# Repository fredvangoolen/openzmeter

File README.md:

Description
===============

openzmeter (oZm) is an Open Source system designed for power quality analysis and smart energy metering in power networks.
It has been designed to comply with international standards IEC 61000-4-30 and EN 50160. It is able to measure RMS voltages with an accuracy up to 0.1%, frequency up to 10 mHz (between 42.5 and 57.5 Hz) and RMS currents according to different sensor probes (the basic version can handle up to 400 V and 50 A RMS using an onboard Hall effect sensor with a precision of 1%).

See http://www.openzmeter.com

Fluvius digital meter (S1 port) support
===============

This fork adds support for the **S1 port** of the digital electricity meters installed by Fluvius in Flanders
(Belgium). Instead of openZmeter's own capture hardware, the meter itself provides the measurements: it continuously
streams instantaneous voltage and current samples of all phases (and the neutral, if the meter provides it), at
2 to 4 kHz. openZmeter analyzes these samples like those from its own hardware, giving RMS values, active/reactive
power and energy, frequency, harmonics, events, alarms, cyclic histograms, MQTT and tariffs.

* **Specification**: e-MUCS H ed. 1.3, section 4, published by
  [Fluvius](https://www.fluvius.be/sites/fluvius/files/2019-12/e-mucs_h_ed_1_3.pdf).
* **Activation**: the S1 port is off by default. Ask Fluvius to activate it for your meter.
* **Hardware**: a USB to RS-422 adapter that can receive at exactly 2 Mbaud (e.g. FTDI FT232R/FT232H based) connected
  to the RJ12 S1 socket of the meter: pin 3 = GND, pin 4 = BUS- and pin 5 = BUS+. The line needs one 120 Ω termination
  on the adapter side (built into the FTDI USB-RS422-WE cable). Check the pin numbering first: on the Sagemcom meter
  tested here, pin 1 is the **rightmost** contact when facing the socket. Wire colours for the FTDI USB-RS422-WE cable
  are in the [S1 driver README](Service/Source/Devices/S1/README.md#wiring-an-ftdi-usb-rs422-we-cable).
* **Check the connection first**: [`Service/Utils/S1Monitor`](Service/Utils/S1Monitor) is a small standalone tool
  (only needs `g++`). It shows frame rate, errors, meter info, frequency, RMS values and power every second, and
  explains what is wrong when nothing valid arrives. Build it with `make` and run `./s1monitor /dev/ttyUSB0`.
* **Check the results**: [`Service/Utils/P1Monitor`](Service/Utils/P1Monitor) reads the P1 port of the same meter and
  compares its voltage, current, power and energy registers with what openZmeter measured on S1.
* **Tests without a meter**: [`Service/Utils/S1Test`](Service/Utils/S1Test) has unit tests and a simulated meter.
* **Single board computer**: a Raspberry Pi 4 (2 GB is enough) works well. Run
  `sudo Service/Packaging/raspberrypi/install.sh` to build and install openZmeter with a local PostgreSQL database,
  a systemd service and a watchdog that restarts openZmeter when its web interface stops answering. Then enable the
  device under *Settings » Devices » S1*. If port 80 is already taken (for example by Pi-hole), add `--http-port 8080`.
* **Analyzer**: created when the first valid frame arrives, as "Fluvius S1 meter" with time zone Europe/Brussels. Both
  can be changed in its settings.
* **Clock**: the meter announces its sample rate only roughly, so the driver measures it against the system clock. Keep
  the clock synchronized (NTP, the default on Raspberry Pi OS).
* **Limitations**: because of the lower sample rate, harmonics above roughly the 25th to 40th order (depending on the
  meter) are reported as 0.

Details are in the [S1 driver README](Service/Source/Devices/S1/README.md). Architecture, data flow and storage
notes are in [`Docs/NOTES.md`](Docs/NOTES.md).

License and changes
===============

This is a **modified version of openZmeter**. The original is [eauel/openzmeter](https://github.com/eauel/openzmeter)
([openzmeter.com](https://openzmeter.com)). Modified by [fredvangoolen](https://github.com/fredvangoolen) since
19 November 2026: support for the S1 port of Fluvius digital meters, an installer for the Raspberry Pi, test tools, and
corrections to existing calculations (listed in [`Docs/NOTES.md`](Docs/NOTES.md)). The commit history has all changes
with their dates.

Like the original, it is licensed under the GNU General Public License, version 3 or (as stated in the source files) any
later version: see [`LICENSE`](LICENSE). It comes without any warranty. Libraries in `Service/Libs` have their own licenses, included there.

This project is not affiliated with or endorsed by Fluvius, FTDI or the makers of openZmeter. Product names are only used
to describe what it works with.

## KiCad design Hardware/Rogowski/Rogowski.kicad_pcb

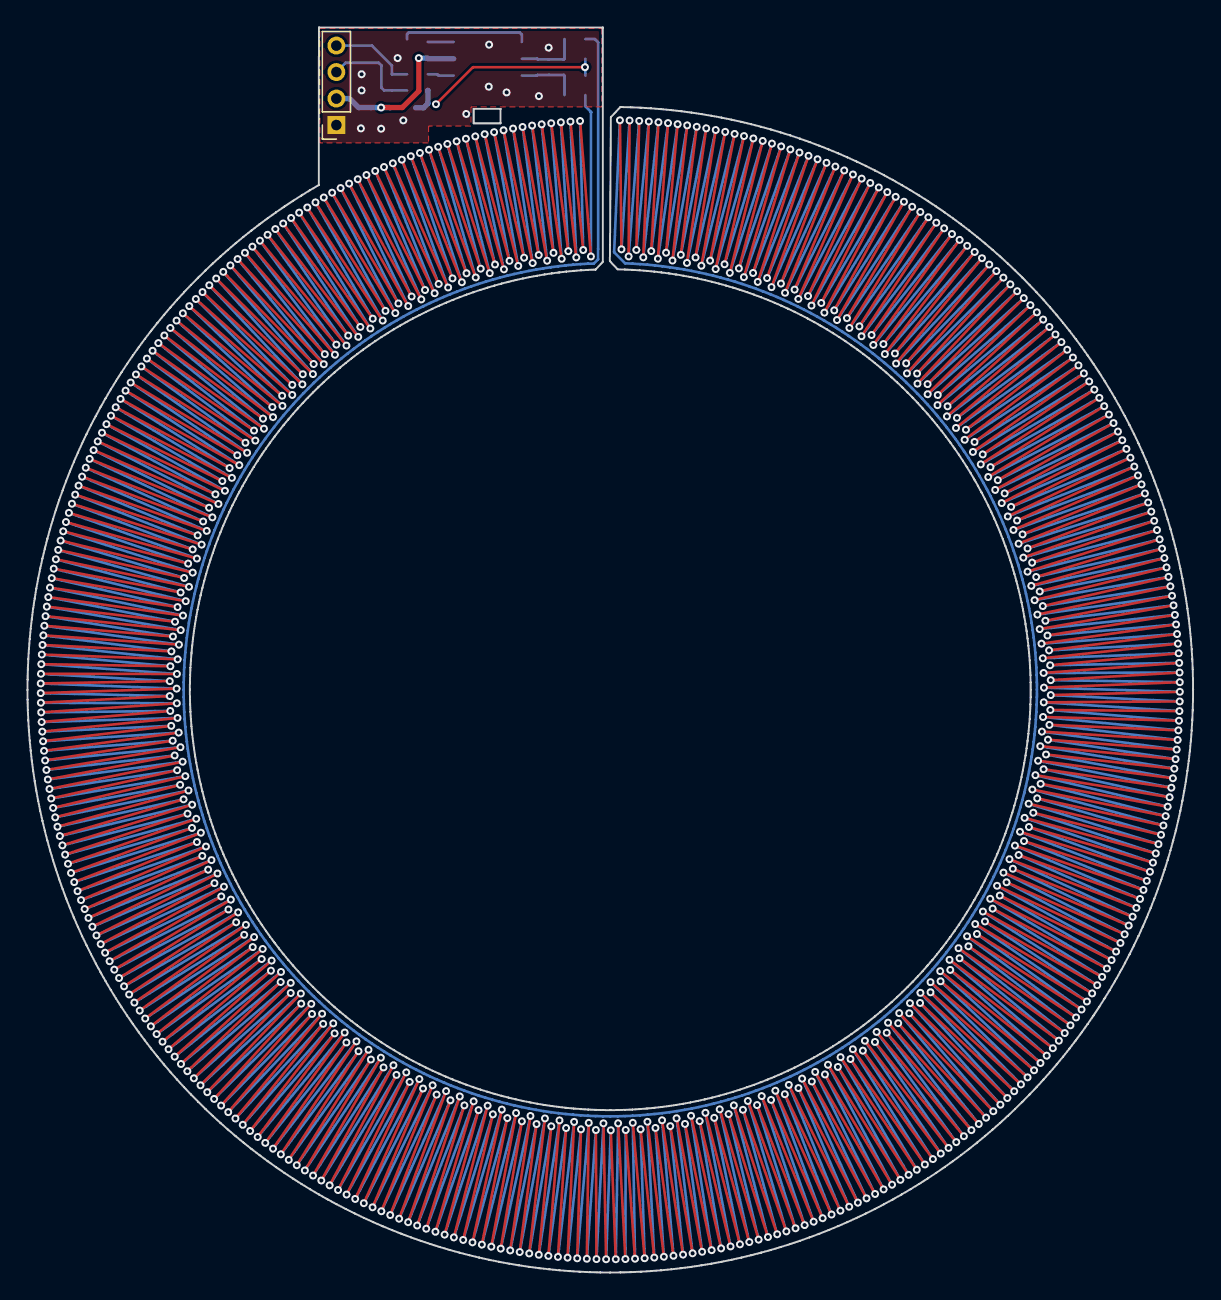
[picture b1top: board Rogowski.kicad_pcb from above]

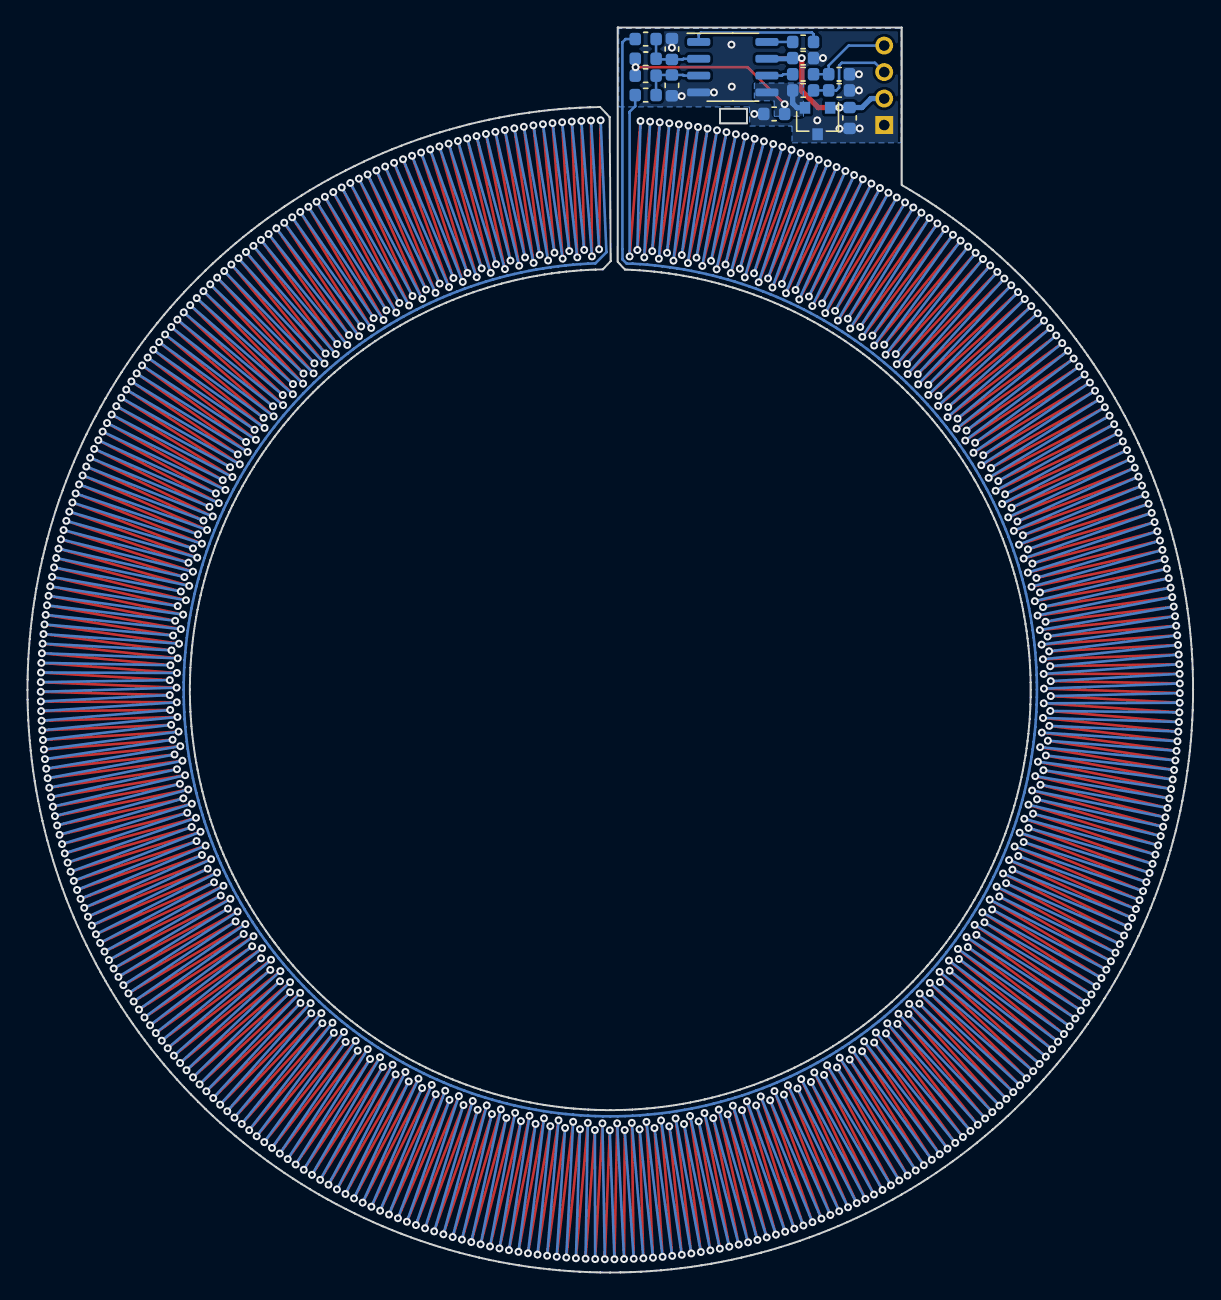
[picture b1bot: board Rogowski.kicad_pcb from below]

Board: 2 copper layers, 88.0 x 94.0 mm, 17 parts (16 on the bottom side), 11 nets.

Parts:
C1, C2, C3, C4, C5, C6, C7: C_Small; C_0603_1608Metric
J1: Conn_01x04_Female; PinSocket_1x04_P2.00mm_Vertical
R1, R2, R3, R4, R5, R6, R7: R_Small; R_0603_1608Metric
U1: INA128; SO-8_3.9x4.9mm_P1.27mm
U2: MCP1525-TT; SOT-23

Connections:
2.5V: C7.2, R3.1, R4.2, R7.2, U1.5, U2.2
5V: C3.2, C4.2, J1.2, U1.7, U2.1
GND: C1.2, C2.1, C3.1, C4.1, C5.2, C6.1, C7.1, J1.1, U1.4, U2.3
unnamed: C1.1, R1.1, R3.2, U1.3
unnamed: C2.2, R2.1, R4.1, U1.2
unnamed: C5.1, J1.4, R6.1
unnamed: C6.2, J1.3, R7.1
unnamed: R1.2, R2.2
unnamed: R5.1, U1.8
unnamed: R5.2, U1.1
unnamed: R6.2, U1.6

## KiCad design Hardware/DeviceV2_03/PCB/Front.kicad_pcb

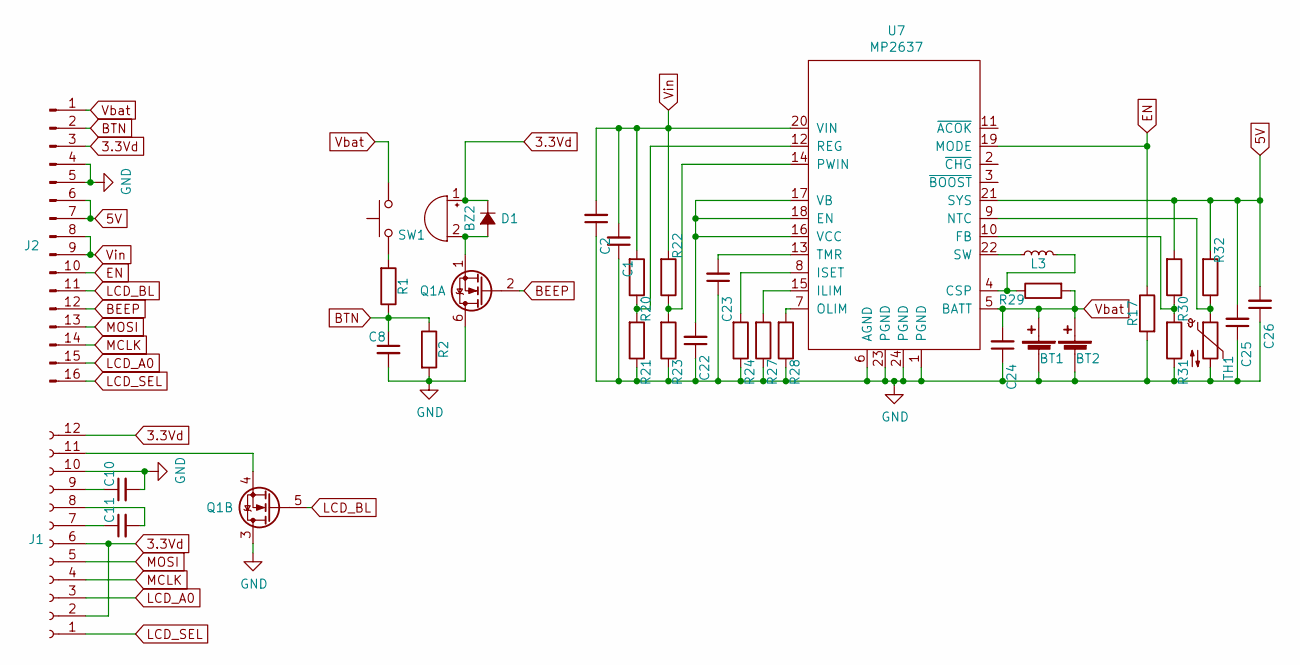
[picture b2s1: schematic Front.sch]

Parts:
BT1, BT2: Battery clips; 18500_Clips
BZ2: QMB-09B-05; MLT-5030
C1, C2, C25, C26: 100nF 25v; C_0805_2012Metric
C8, C10, C11, C22, C23, C24: 100nF 25v; C_0603_1608Metric
D1: D_Small_ALT-3Phase-rescue; D_SOD-323
J1: Conn_01x12_Female; LCD_52.3x40.2
J2: Conn_01x06_Male; PinHeader_1x16_P2.54mm_Vertical
L3: L_Small; MWSA0503S
Q1: SSM6N7002KFU; SOT-363_SC-70-6
R1, R2, R17, R20, R21, R22, R23, R24, R27, R28, R30, R31, R32: 100k; R_0603_1608Metric
R29: 100k; R_1206_3216Metric
SW1: SW_Push-3Phase-rescue; SW_Push_4.5x4.5mm_H8mm
TH1: Thermistor_NTC-3Phase-rescue; R_0603_1608Metric
U7: MP2637; QFN-24_4x4mm_P0.5mm

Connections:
3.3Vd: BZ2.1 (-), D1.1 (K), J1.2, J1.6, J1.12, J2.3
5V: C25.2, C26.2, J2.6, J2.7, R30.2, R32.2, U7.21 (SYS)
BEEP: J2.12, Q1.2 (G)
BTN: C8.1, J2.2, R1.1, R2.1
EN: J2.10, R17.1, U7.19 (MODE)
GND: BT1.2 (-), BT2.2 (-), C1.1, C2.1, C8.2, C10.2, C22.1, C23.1, C24.1, C25.1, C26.1, J1.10, J2.4, J2.5, Q1.3 (D), Q1.6 (D), R2.2, R17.2, R21.1, R23.1, R24.1, R27.1, R28.1, R31.1, TH1.2, U7.1 (PGND), U7.6 (AGND), U7.23 (PGND), U7.24 (PGND)
LCD_A0: J1.3, J2.15
LCD_BL: J2.11, Q1.5 (G)
LCD_SEL: J1.1, J2.16
MCLK: J1.4, J2.14
MOSI: J1.5, J2.13
unnamed: BZ2.2 (+), D1.2 (A), Q1.1 (S)
unnamed: C10.1, J1.9
unnamed: C11.1, J1.7
unnamed: C11.2, J1.8
unnamed: C22.2, U7.16 (VCC), U7.17 (VB), U7.18 (EN)
unnamed: C23.2, U7.13 (TMR)
unnamed: J1.11, Q1.4 (S)
unnamed: L3.1, R29.1, U7.4 (CSP)
unnamed: L3.2, U7.22 (SW)
unnamed: R1.2, SW1.2
unnamed: R20.1, R21.2, U7.12 (REG)
unnamed: R22.1, R23.2, U7.14 (PWIN)
unnamed: R24.2, U7.8 (ISET)
unnamed: R27.2, U7.15 (ILIM)
unnamed: R28.2, U7.7 (OLIM)
unnamed: R30.1, R31.2, U7.10 (FB)
unnamed: R32.1, TH1.1, U7.9 (NTC)
Vbat: BT1.1 (+), BT2.1 (+), C24.2, J2.1, R29.2, SW1.1, U7.5 (BATT)
Vin: C1.2, C2.2, J2.8, J2.9, R20.2, R22.2, U7.20 (VIN)

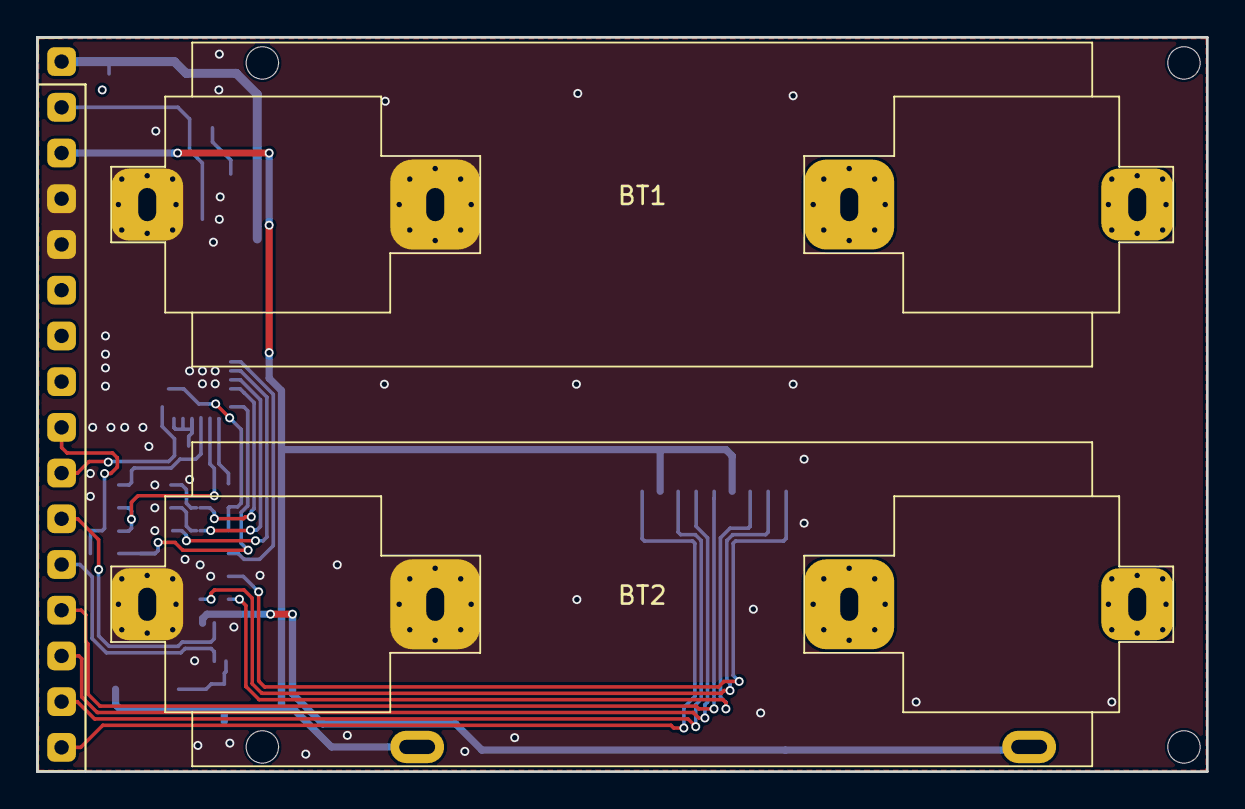
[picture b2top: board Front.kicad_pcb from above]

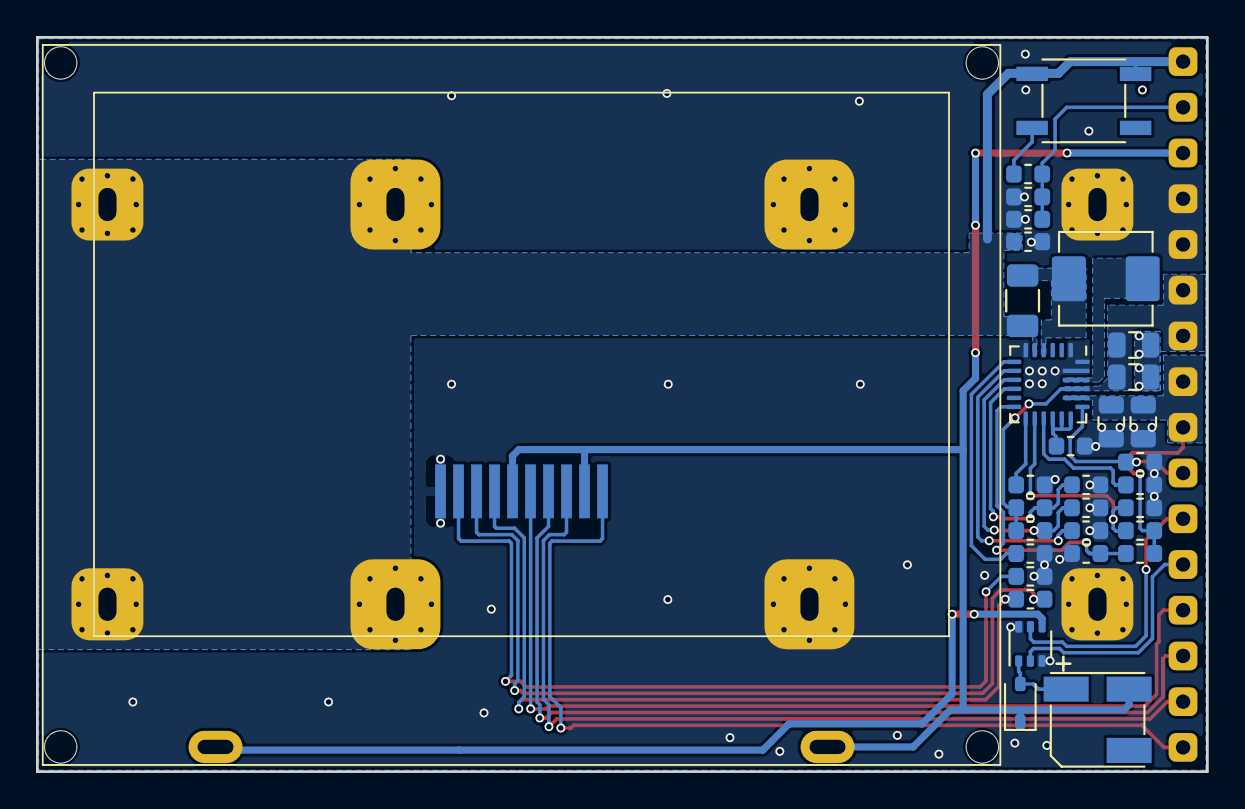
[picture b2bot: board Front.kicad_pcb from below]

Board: 2 copper layers, 65.0 x 40.8 mm, 35 parts (32 on the bottom side), 30 nets.

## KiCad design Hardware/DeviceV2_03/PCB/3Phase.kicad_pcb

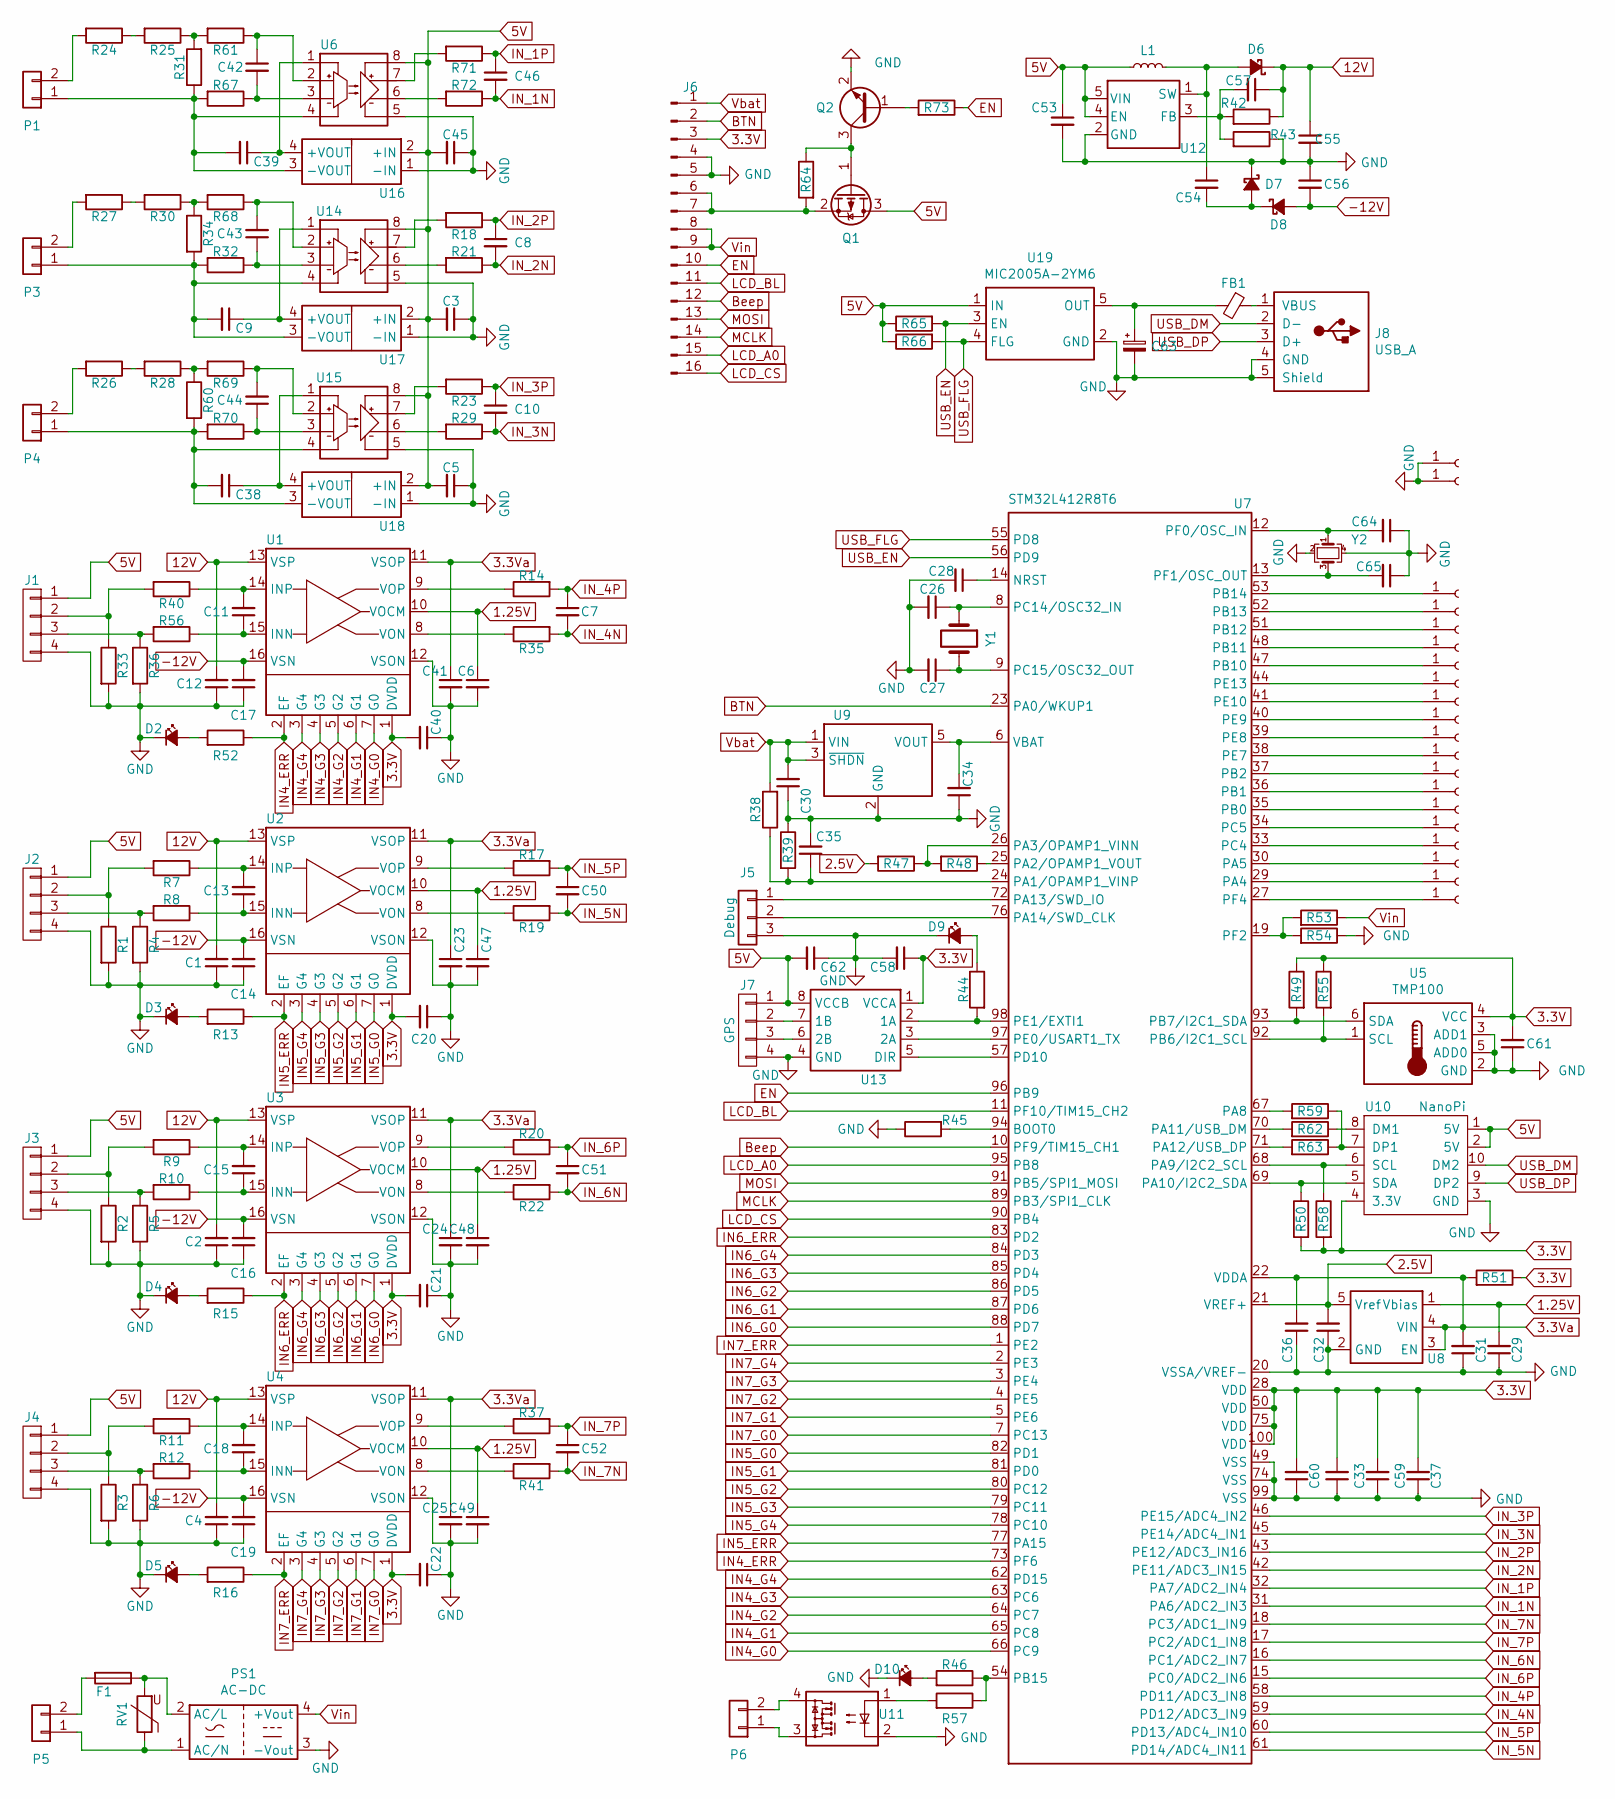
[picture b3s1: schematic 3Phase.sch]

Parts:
C1, C2, C3, C4, C5, C6, C7, C9, C11, C12, C13, C14, C15, C16, C17, C18, C19, C20, C21, C22, C23, C24, C25, C28, C29, C30, C31, C32, C33, C34, C35, C36, C37, C38, C40, C41, C43, C44, C45, C47, C48, C49, C50, C51, C52, C53, C54, C55, C56, C57, C59, C60, C61: 100nF 25v; C_0603_1608Metric
C8, C10, C42, C46: 330pF NP0; C_0603_1608Metric
C26, C27: 6pF; C_0603_1608Metric; LCSC C130125
C39: 100nF 10v; C_0603_1608Metric
C58, C62: 100nF; C_0603_1608Metric; LCSC C14663
C63: CP_Small; CP_EIA-3528-21_Kemet-B
C64, C65: 20pF; C_0603_1608Metric; LCSC C105621
D2, D10: LED_Small_ALT; LED_0603_1608Metric
D3, D4, D5, D9: LED; LED_0603_1608Metric; LCSC C1322294
D6, D7, D8: D_Schottky_Small_ALT; D_SOD-323
F1: Fuse; Fuse_Littelfuse_395Series
FB1: BLM18KG601SZ1D; L_0603_1608Metric
J1, J2, J3, J4, J7: 95001-6P6C; KF2EDGR_2.54x4
J5: 95001-6P6C; PinHeader_1x03_P2.54mm_Vertical
J6: Conn_01x16_Male; PinHeader_1x16_P2.54mm_Vertical
J8: USB_A; USB_A_Molex_67643_Horizontal
J9, J10, J11, J12, J13, J14, J15, J16, J17, J20, J22, J23, J25, J26, J27, J28, J29, J30, J31, J32: Conn_01x01_Female; TestPoint_1.8mm
L1: L_Small; L_1210_3225Metric
P1, P3, P4, P5, P6: 3.81x4 terminal block; PhoenixContact_MC_1,5_2-G-3.81_1x02_P3.81mm_Horizontal
PS1: AC-DC; AC-DC_Aliexpress
Q1: Si2319CDS; SOT-23
Q2: MMBT3904; SOT-23
R1, R2, R3, R4, R5, R6, R7, R8, R9, R10, R11, R12, R32, R33, R34, R36, R38, R39, R40, R42, R43, R45, R46, R47, R48, R49, R51, R53, R54, R55, R56, R57, R59, R60, R62, R63, R64, R65, R66, R68, R69, R70, R73: 2.2k; R_0603_1608Metric
R13, R15, R16, R44, R52: 470; R_0603_1608Metric; LCSC C114669
R14, R17, R19, R20, R22, R35, R37, R41: 100h; R_0603_1608Metric
R18, R21, R23, R29, R61, R67, R71, R72: 12; R_0603_1608Metric
R24, R25: 499k; R_1206_3216Metric; LCSC C517514
R26, R27, R28, R30: 200k; R_1206_3216Metric
R31: 1k02; R_0603_1608Metric; LCSC C705734
R50, R58: 4k7; R_0603_1608Metric; LCSC C99782
RV1: 05D391K; RV_Disc_D7mm_W3.4mm_P5mm
U1, U2, U3, U4: PGA281; TSSOP-16_4.4x5mm_P0.65mm; LCSC C69359
U5: TMP100; SOT-23-6
U6, U14, U15: SI8921BB; SOIC-8_3.9x4.9mm_P1.27mm
U7: STM32L412R8T6; LQFP-100_14x14mm_P0.5mm
U8: REF2025; SOT-23-5
U9: MCP1811; SOT-23-5
U10: NanoPi; NanoPI_Air
U11: SSR_MOSFET_DIP4; DIP-4_W7.62mm
U12: LM27313XMF; SOT-23-5
U13: SN74LVC2T45DCUTG4; VSSOP-8_2.3x2mm_P0.5mm; LCSC C2677407
U16, U17, U18: B0505D-1W; Converter_DCDC_muRata_CRE1xxxxxx3C_THT
U19: MIC2005A-2YM6; SOT-23-5
Y1: 32.768kHz; Crystal_SMD_3215-2Pin_3.2x1.5mm; LCSC C94673
Y2: 8MHz; Crystal_SMD_3225-4Pin_3.2x2.5mm; LCSC C389817

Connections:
1.25V: C6.1, C29.2, C47.1, C48.1, C49.1, U1.10 (VOCM), U2.10 (VOCM), U3.10 (VOCM), U4.10 (VOCM), U8.1 (Vbias)
2.5V: C32.2, R47.2, U7.21 (VREF+), U8.5 (Vref)
3.3V: C20.2, C21.2, C22.2, C33.2, C37.2, C40.2, C58.1, C59.2, C60.2, C61.2, J6.3, R49.1, R50.2, R51.1, R55.1, R58.2, U1.1 (DVDD), U2.1 (DVDD), U3.1 (DVDD), U4.1 (DVDD), U5.4 (VCC), U7.28 (VDD), U7.50 (VDD), U7.75 (VDD), U7.100 (VDD), U10.4 (3.3V), U13.1 (VCCA)
3.3Va: C23.1, C24.1, C25.1, C31.2, C36.2, C41.1, R51.2, U1.11 (VSOP), U2.11 (VSOP), U3.11 (VSOP), U4.11 (VSOP), U7.22 (VDDA), U8.3 (EN), U8.4 (VIN)
5V: C3.2, C5.2, C45.2, C53.1, C62.2, J1.1, J2.1, J3.1, J4.1, J7.1, L1.1, Q1.3 (D), R65.1, R66.1, U6.8 (VDD2), U10.1 (5V), U10.2 (5V), U12.4 (EN), U12.5 (VIN), U13.8 (VCCB), U14.8 (VDD2), U15.8 (VDD2), U16.2 (+IN), U17.2 (+IN), U18.2 (+IN), U19.1 (IN)
12V: C1.2, C2.2, C4.2, C12.2, C55.1, C57.1, D6.1 (K), R42.1, U1.13 (VSP), U2.13 (VSP), U3.13 (VSP), U4.13 (VSP)
-12V: C14.2, C16.2, C17.2, C19.2, C56.2, D8.2 (A), U1.16 (VSN), U2.16 (VSN), U3.16 (VSN), U4.16 (VSN)
BTN: J6.2, U7.23 (PA0/WKUP1)
Beep: J6.12, U7.10 (PF9/TIM15_CH1)
EN: J6.10, R73.1, U7.96 (PB9)
GND: C1.1, C2.1, C3.1, C4.1, C5.1, C6.2, C12.1, C14.1, C16.1, C17.1, C19.1, C20.1, C21.1, C22.1, C23.2, C24.2, C25.2, C26.2, C27.2, C28.2, C29.1, C30.1, C31.1, C32.1, C33.1, C34.1, C35.2, C36.1, C37.1, C40.1, C41.2, C45.1, C47.2, C48.2, C49.2, C53.2, C55.2, C56.1, C58.2, C59.1, C60.1, C61.1, C62.1, C63.2, C64.1, C65.1, D2.1 (K), D3.1 (K), D4.1 (K), D5.1 (K), D7.1 (K), D9.1 (K), D10.1 (K), J1.4, J2.4, J3.4, J4.4, J5.3, J6.4, J6.5, J7.4, J8.4 (GND), J8.5 (Shield), J17.1, J32.1, PS1.3 (-Vout), Q2.2 (E), R1.2, R2.2, R3.2, R4.2, R5.2, R6.2, R33.2, R36.2, R39.1, R43.1, R45.1, R54.1, U1.12 (VSON), U2.12 (VSON), U3.12 (VSON), U4.12 (VSON), U5.2 (GND), U5.3 (ADD1), U5.5 (ADD0), U6.5 (GND2), U7.20 (VSSA/VREF-), U7.49 (VSS), U7.74 (VSS), U7.99 (VSS), U8.2 (GND), U9.2 (GND), U10.3 (GND), U11.2, U12.2 (GND), U13.4 (GND), U14.5 (GND2), U15.5 (GND2), U16.1 (-IN), U17.1 (-IN), U18.1 (-IN), U19.2 (GND), Y2.2, Y2.4
IN4_ERR: R52.1, U1.2 (EF), U7.73 (PF6)
IN4_G0: U1.7 (G0), U7.66 (PC9)
IN4_G1: U1.6 (G1), U7.65 (PC8)
IN4_G2: U1.5 (G2), U7.64 (PC7)
IN4_G3: U1.4 (G3), U7.63 (PC6)
IN4_G4: U1.3 (G4), U7.62 (PD15)
IN5_ERR: R13.1, U2.2 (EF), U7.77 (PA15)
IN5_G0: U2.7 (G0), U7.82 (PD1)
IN5_G1: U2.6 (G1), U7.81 (PD0)
IN5_G2: U2.5 (G2), U7.80 (PC12)
IN5_G3: U2.4 (G3), U7.79 (PC11)
IN5_G4: U2.3 (G4), U7.78 (PC10)
IN6_ERR: R15.1, U3.2 (EF), U7.83 (PD2)
IN6_G0: U3.7 (G0), U7.88 (PD7)
IN6_G1: U3.6 (G1), U7.87 (PD6)
IN6_G2: U3.5 (G2), U7.86 (PD5)
IN6_G3: U3.4 (G3), U7.85 (PD4)
IN6_G4: U3.3 (G4), U7.84 (PD3)
IN7_ERR: R16.1, U4.2 (EF), U7.1 (PE2)
IN7_G0: U4.7 (G0), U7.7 (PC13)
IN7_G1: U4.6 (G1), U7.5 (PE6)
IN7_G2: U4.5 (G2), U7.4 (PE5)
IN7_G3: U4.4 (G3), U7.3 (PE4)
IN7_G4: U4.3 (G4), U7.2 (PE3)
IN_1N: C46.2, R72.1, U7.31 (PA6/ADC2_IN3)
IN_1P: C46.1, R71.1, U7.32 (PA7/ADC2_IN4)
IN_2N: C8.2, R21.1, U7.42 (PE11/ADC3_IN15)
IN_2P: C8.1, R18.1, U7.43 (PE12/ADC3_IN16)
IN_3N: C10.2, R29.1, U7.45 (PE14/ADC4_IN1)
IN_3P: C10.1, R23.1, U7.46 (PE15/ADC4_IN2)
IN_4N: C7.2, R35.2, U7.59 (PD12/ADC3_IN9)
IN_4P: C7.1, R14.2, U7.58 (PD11/ADC3_IN8)
IN_5N: C50.2, R19.2, U7.61 (PD14/ADC4_IN11)
IN_5P: C50.1, R17.2, U7.60 (PD13/ADC4_IN10)
IN_6N: C51.2, R22.2, U7.16 (PC1/ADC2_IN7)
IN_6P: C51.1, R20.2, U7.15 (PC0/ADC2_IN6)
IN_7N: C52.2, R41.2, U7.18 (PC3/ADC1_IN9)
IN_7P: C52.1, R37.2, U7.17 (PC2/ADC1_IN8)
LCD_A0: J6.15, U7.95 (PB8)
LCD_BL: J6.11, U7.11 (PF10/TIM15_CH2)
LCD_CS: J6.16, U7.90 (PB4)
MCLK: J6.14, U7.89 (PB3/SPI1_CLK)
MOSI: J6.13, U7.91 (PB5/SPI1_MOSI)
unnamed: C9.1, U14.1 (VDD1), U17.4 (+VOUT)
unnamed: C9.2, P3.1, R32.2, R34.2, U14.4 (GND1), U17.3 (-VOUT)
unnamed: C11.1, R56.1, U1.15 (INN)
unnamed: C11.2, R40.1, U1.14 (INP)
unnamed: C13.1, R8.1, U2.15 (INN)
unnamed: C13.2, R7.1, U2.14 (INP)
unnamed: C15.1, R10.1, U3.15 (INN)
unnamed: C15.2, R9.1, U3.14 (INP)
unnamed: C18.1, R12.1, U4.15 (INN)
unnamed: C18.2, R11.1, U4.14 (INP)
unnamed: C26.1, U7.8 (PC14/OSC32_IN), Y1.1
unnamed: C27.1, U7.9 (PC15/OSC32_OUT), Y1.2
unnamed: C28.1, U7.14 (NRST)
unnamed: C34.2, U7.6 (VBAT), U9.5 (VOUT)
unnamed: C35.1, R38.1, R39.2, U7.24 (PA1/OPAMP1_VINP)
unnamed: C38.1, U15.1 (VDD1), U18.4 (+VOUT)
unnamed: C38.2, P4.1, R60.2, R70.2, U15.4 (GND1), U18.3 (-VOUT)
unnamed: C39.1, U6.1 (VDD1), U16.4 (+VOUT)
unnamed: C39.2, P1.1, R31.1, R67.2, U6.4 (GND1), U16.3 (-VOUT)
unnamed: C42.1, R61.1, U6.2 (IN+)
unnamed: C42.2, R67.1, U6.3 (IN-)
unnamed: C43.1, R32.1, U14.3 (IN-)
unnamed: C43.2, R68.1, U14.2 (IN+)
unnamed: C44.1, R70.1, U15.3 (IN-)
unnamed: C44.2, R69.1, U15.2 (IN+)
unnamed: C54.1, D6.2 (A), L1.2, U12.1 (SW)
unnamed: C54.2, D7.2 (A), D8.1 (K)
unnamed: C57.2, R42.2, R43.2, U12.3 (FB)
unnamed: C63.1, FB1.2, U19.5 (OUT)
unnamed: C64.2, U7.12 (PF0/OSC_IN), Y2.1
unnamed: C65.2, U7.13 (PF1/OSC_OUT), Y2.3
unnamed: D2.2 (A), R52.2
unnamed: D3.2 (A), R13.2
unnamed: D4.2 (A), R15.2
unnamed: D5.2 (A), R16.2
unnamed: D9.2 (A), R44.1
unnamed: D10.2 (A), R46.2
unnamed: F1.1, PS1.2 (AC/L), RV1.2
unnamed: F1.2, P5.2
unnamed: FB1.1, J8.1 (VBUS)
unnamed: J1.2, R33.1, R40.2
unnamed: J1.3, R36.1, R56.2
unnamed: J2.2, R1.1, R7.2
unnamed: J2.3, R4.1, R8.2
unnamed: J3.2, R2.1, R9.2
unnamed: J3.3, R5.1, R10.2
unnamed: J4.2, R3.1, R11.2
unnamed: J4.3, R6.1, R12.2
unnamed: J5.1, U7.72 (PA13/SWD_IO)
unnamed: J5.2, U7.76 (PA14/SWD_CLK)
unnamed: J6.6, J6.7, Q1.2 (S), R64.2
unnamed: J7.2, U13.7 (1B)
unnamed: J7.3, U13.6 (2B)
unnamed: J9.1, U7.37 (PB2)
unnamed: J10.1, U7.36 (PB1)
unnamed: J11.1, U7.35 (PB0)
unnamed: J12.1, U7.34 (PC5)
unnamed: J13.1, U7.33 (PC4)
unnamed: J14.1, U7.30 (PA5)
unnamed: J15.1, U7.29 (PA4)
unnamed: J16.1, U7.27 (PF4)
unnamed: J20.1, U7.52 (PB13)
unnamed: J22.1, U7.53 (PB14)
unnamed: J23.1, U7.51 (PB12)
unnamed: J25.1, U7.48 (PB11)
unnamed: J26.1, U7.47 (PB10)
unnamed: J27.1, U7.44 (PE13)
unnamed: J28.1, U7.41 (PE10)
unnamed: J29.1, U7.40 (PE9)
unnamed: J30.1, U7.39 (PE8)
unnamed: J31.1, U7.38 (PE7)
unnamed: P1.2, R24.2
unnamed: P3.2, R27.2
unnamed: P4.2, R26.2
unnamed: P5.1, PS1.1 (AC/N), RV1.1
unnamed: P6.1, U11.3
unnamed: P6.2, U11.4
unnamed: Q1.1 (G), Q2.3 (C), R64.1
unnamed: Q2.1 (B), R73.2
unnamed: R14.1, U1.9 (VOP)
unnamed: R17.1, U2.9 (VOP)
unnamed: R18.2, U14.7 (OUT+)
unnamed: R19.1, U2.8 (VON)
unnamed: R20.1, U3.9 (VOP)
unnamed: R21.2, U14.6 (OUT-)
unnamed: R22.1, U3.8 (VON)
unnamed: R23.2, U15.7 (OUT+)
unnamed: R24.1, R25.2
unnamed: R25.1, R31.2, R61.2
unnamed: R26.1, R28.2
unnamed: R27.1, R30.2
unnamed: R28.1, R60.1, R69.2
unnamed: R29.2, U15.6 (OUT-)
unnamed: R30.1, R34.1, R68.2
unnamed: R35.1, U1.8 (VON)
unnamed: R37.1, U4.9 (VOP)
unnamed: R41.1, U4.8 (VON)
unnamed: R44.2, U7.98 (PE1/EXTI1), U13.2 (1A)
unnamed: R45.2, U7.94 (BOOT0)
unnamed: R46.1, R57.1, U7.54 (PB15)
unnamed: R47.1, R48.2, U7.26 (PA3/OPAMP1_VINN)
unnamed: R48.1, U7.25 (PA2/OPAMP1_VOUT)
unnamed: R49.2, U5.6 (SDA), U7.93 (PB7/I2C1_SDA)
unnamed: R50.1, U7.69 (PA10/I2C2_SDA), U10.5 (SDA)
unnamed: R53.2, R54.2, U7.19 (PF2)
unnamed: R55.2, U5.1 (SCL), U7.92 (PB6/I2C1_SCL)
unnamed: R57.2, U11.1
unnamed: R58.1, U7.68 (PA9/I2C2_SCL), U10.6 (SCL)
unnamed: R59.1, R63.1, U10.7 (DP1)
unnamed: R59.2, U7.67 (PA8)
unnamed: R62.1, U10.8 (DM1)
unnamed: R62.2, U7.70 (PA11/USB_DM)
unnamed: R63.2, U7.71 (PA12/USB_DP)
unnamed: R71.2, U6.7 (OUT+)
unnamed: R72.2, U6.6 (OUT-)
unnamed: U7.97 (PE0/USART1_TX), U13.3 (2A)
unnamed: U7.57 (PD10), U13.5 (DIR)
USB_DM: J8.2 (D-), U10.10 (DM2)
USB_DP: J8.3 (D+), U10.9 (DP2)
USB_EN: R65.2, U7.56 (PD9), U19.3 (EN)
USB_FLG: R66.2, U7.55 (PD8), U19.4 (FLG)
Vbat: C30.2, J6.1, R38.2, U9.1 (VIN), U9.3 (~SHDN)
Vin: J6.8, J6.9, PS1.4 (+Vout), R53.1

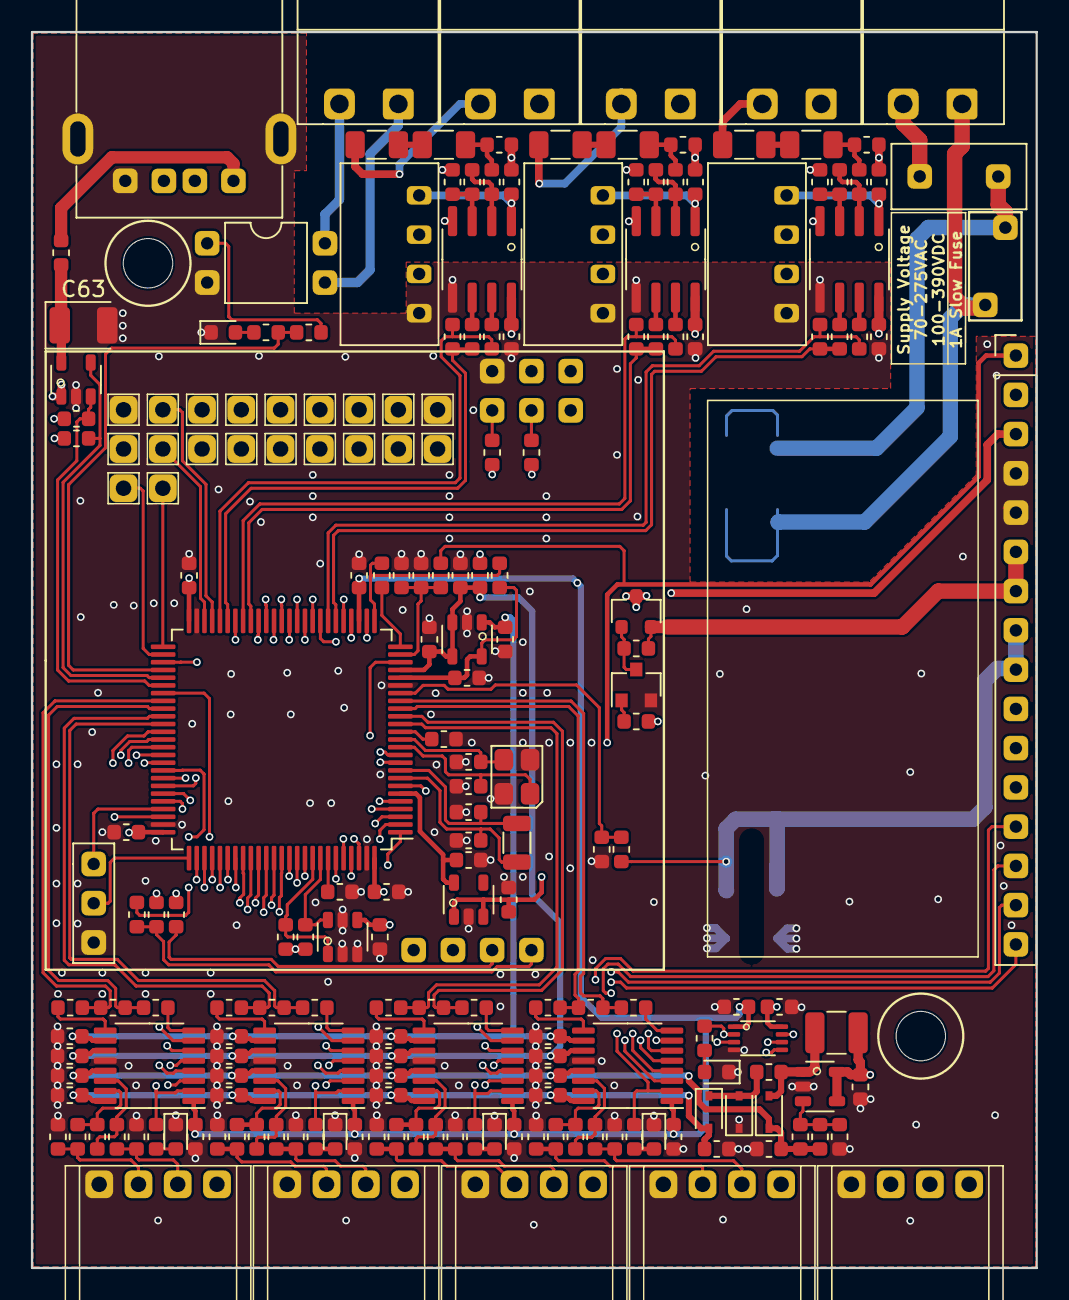
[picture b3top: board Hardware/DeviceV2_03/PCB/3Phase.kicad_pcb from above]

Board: 4 copper layers, 65.0 x 80.0 mm, 209 parts (0 on the bottom side), 177 nets.

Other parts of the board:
‣: MountingHole_3.2mm_M3

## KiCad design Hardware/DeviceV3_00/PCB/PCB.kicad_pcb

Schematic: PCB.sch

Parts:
C1, C3, C4, C5, C6, C7, C8, C9, C17: 10nF; C_0603_1608Metric
C2, C10, C11, C12, C13, C14, C15, C16, C18, C20, C21, C22, C23, C24: 100nF; C_0603_1608Metric
C19, C25: 100uF 10v; CP_Elec_5x5.4
D1, D2: LED_Small_ALT; D_0603_1608Metric
J1: USB_B_Mini; USB_Mini-B_Lumberg_2486_01_Horizontal
J2: Conn_01x02_Female; TerminalBlock_WAGO_804-102_1x02_P5.00mm_45Degree
J3: Conn_01x04_Male; PinHeader_2x02_P2.54mm_Vertical
PS1: F05_N-1WR3; Converter_DCDC_F0505N-1WR3
R1, R2, R3, R4, R6, R7, R8: 200k; R_1206_3216Metric
R5: 3k01; R_0603_1608Metric
R9, R13: 47k; R_0603_1608Metric
R10: 100; R_0603_1608Metric
R11, R12, R14: 2k2; R_0603_1608Metric
U1, U2, U3, U4, U5, U6, U7, U8: ACS725KMATR-30AU-T; SOIC-16W_7.5x10.3mm_P1.27mm
U9: STM32F042F6Px; TSSOP-20_4.4x6.5mm_P0.65mm
U10: HCNR200-500E; DIP-8_W7.62mm
U11, U12: LMV321; SOT-23-5
U13: MCP1700-3302E_SOT23; SOT-23

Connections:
+3V3: C2.1, C10.1, C11.1, C12.1, C13.1, C14.1, C15.1, C16.1, C22.1, C23.1, C24.1, C25.1, J3.2, R14.1, U1.10 (VCC), U2.10 (VCC), U3.10 (VCC), U4.10 (VCC), U5.10 (VCC), U6.10 (VCC), U7.10 (VCC), U8.10 (VCC), U9.5 (VDDA), U9.16 (VDD), U13.2 (VO)
+5V: C19.1, C20.1, C21.1, J1.1, PS1.4 (+Vin), U10.6, U12.5 (V+), U13.3 (VI)
+5VL: C18.1, PS1.5 (+Vout), U10.3, U11.5 (V+)
GND: C1.2, C2.2, C3.2, C4.2, C5.2, C6.2, C7.2, C8.2, C9.2, C10.2, C11.2, C12.2, C13.2, C14.2, C15.2, C16.2, C19.2, C20.2, C21.2, C22.2, C23.2, C24.2, C25.2, J1.5, J1.6, J3.1, PS1.1 (-Vin), R11.1, R12.1, R13.2, U1.11 (NC), U1.14 (NC), U1.15 (GND), U2.11 (NC), U2.14 (NC), U2.15 (GND), U3.11 (NC), U3.14 (NC), U3.15 (GND), U4.11 (NC), U4.14 (NC), U4.15 (GND), U5.11 (NC), U5.14 (NC), U5.15 (GND), U6.11 (NC), U6.14 (NC), U6.15 (GND), U7.11 (NC), U7.14 (NC), U7.15 (GND), U8.11 (NC), U8.14 (NC), U8.15 (GND), U9.1 (PB8), U9.15 (VSS), U12.2 (V-), U13.1 (GND)
GND1: C18.2, J2.1, PS1.7 (-Vout), R5.2, U10.1, U11.2 (V-)
I_1: U1.5 (IP-), U1.6 (IP-), U1.7 (IP-), U1.8 (IP-)
I_2: U2.5 (IP-), U2.6 (IP-), U2.7 (IP-), U2.8 (IP-)
I_3: U3.5 (IP-), U3.6 (IP-), U3.7 (IP-), U3.8 (IP-)
I_4: U4.5 (IP-), U4.6 (IP-), U4.7 (IP-), U4.8 (IP-)
I_5: U5.5 (IP-), U5.6 (IP-), U5.7 (IP-), U5.8 (IP-)
I_6: U6.5 (IP-), U6.6 (IP-), U6.7 (IP-), U6.8 (IP-)
I_7: U7.5 (IP-), U7.6 (IP-), U7.7 (IP-), U7.8 (IP-)
I_8: U8.5 (IP-), U8.6 (IP-), U8.7 (IP-), U8.8 (IP-)
unnamed: C1.1, U1.13 (FILTER)
unnamed: C3.1, U2.13 (FILTER)
unnamed: C4.1, U3.13 (FILTER)
unnamed: C5.1, U4.13 (FILTER)
unnamed: C6.1, U5.13 (FILTER)
unnamed: C7.1, U6.13 (FILTER)
unnamed: C8.1, U7.13 (FILTER)
unnamed: C9.1, U8.13 (FILTER)
unnamed: C17.1, R9.1, U11.3 (-)
unnamed: C17.2, R10.2, U11.4
unnamed: D1.1 (K), R11.2
unnamed: D1.2 (A), U9.3 (PF1)
unnamed: D2.1 (K), R12.2
unnamed: D2.2 (A), U9.2 (PF0)
unnamed: J1.2, U9.17 (PA9/PA11)
unnamed: J1.3, U9.18 (PA10/PA12)
unnamed: J2.2, R6.2
unnamed: J3.3, U9.20 (PA14)
unnamed: J3.4, U9.19 (PA13)
unnamed: R1.1, R2.2
unnamed: R1.2, R7.1
unnamed: R2.1, R3.2
unnamed: R3.1, R4.2
unnamed: R4.1, R5.1, U11.1 (+)
unnamed: R6.1, R8.2
unnamed: R7.2, R8.1
unnamed: R9.2, U10.4
unnamed: R10.1, U10.2
unnamed: R13.1, U10.5, U12.1 (+)
unnamed: R14.2, U9.4 (NRST)
O_1: U1.1 (IP+), U1.2 (IP+), U1.3 (IP+), U1.4 (IP+)
O_2: U2.1 (IP+), U2.2 (IP+), U2.3 (IP+), U2.4 (IP+)
O_3: U3.1 (IP+), U3.2 (IP+), U3.3 (IP+), U3.4 (IP+)
O_4: U4.1 (IP+), U4.2 (IP+), U4.3 (IP+), U4.4 (IP+)
O_5: U5.1 (IP+), U5.2 (IP+), U5.3 (IP+), U5.4 (IP+)
O_6: U6.1 (IP+), U6.2 (IP+), U6.3 (IP+), U6.4 (IP+)
O_7: U7.1 (IP+), U7.2 (IP+), U7.3 (IP+), U7.4 (IP+)
O_8: U8.1 (IP+), U8.2 (IP+), U8.3 (IP+), U8.4 (IP+)
Sen1: U1.12 (Iout), U9.9 (PA3)
Sen2: U2.12 (Iout), U9.8 (PA2)
Sen3: U3.12 (Iout), U9.7 (PA1)
Sen4: U4.12 (Iout), U9.6 (PA0)
Sen5: U5.12 (Iout), U9.14 (PB1)
Sen6: U6.12 (Iout), U9.13 (PA7)
Sen7: U7.12 (Iout), U9.12 (PA6)
Sen8: U8.12 (Iout), U9.11 (PA5)
Volt: U9.10 (PA4), U12.3 (-), U12.4

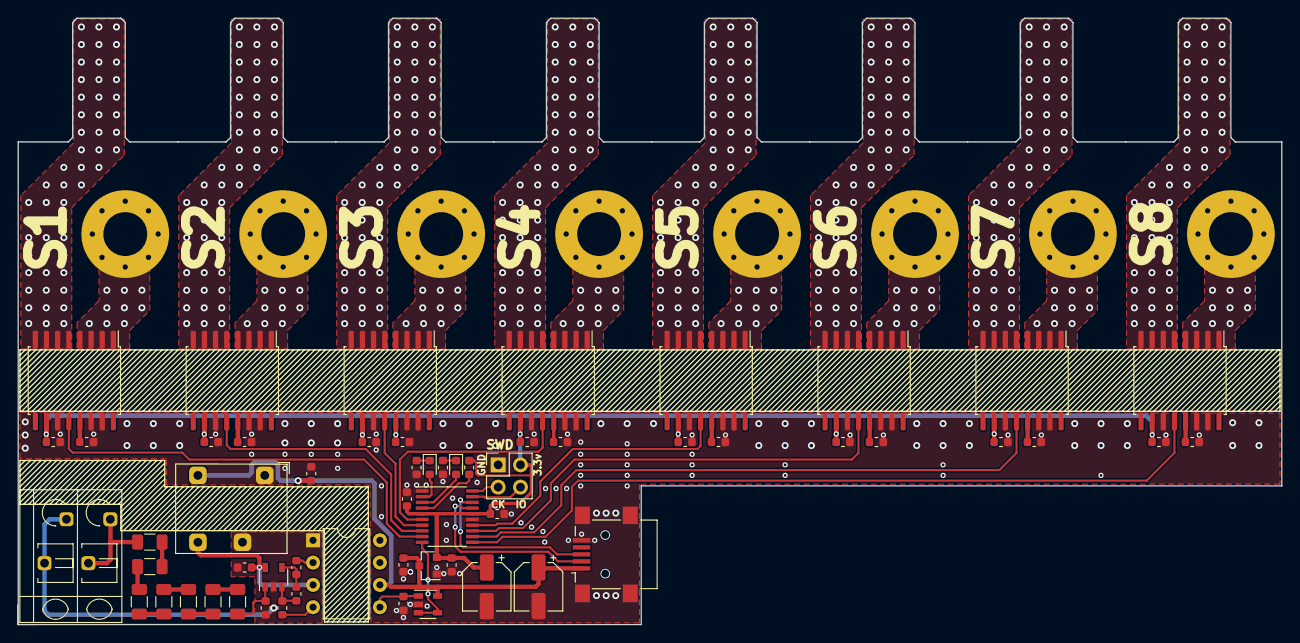
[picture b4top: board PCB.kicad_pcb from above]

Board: 2 copper layers, 144.0 x 69.1 mm, 58 parts (0 on the bottom side), 60 nets.
